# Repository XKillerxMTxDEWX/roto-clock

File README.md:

# roto-clock
Arduino powered spinning clock display.

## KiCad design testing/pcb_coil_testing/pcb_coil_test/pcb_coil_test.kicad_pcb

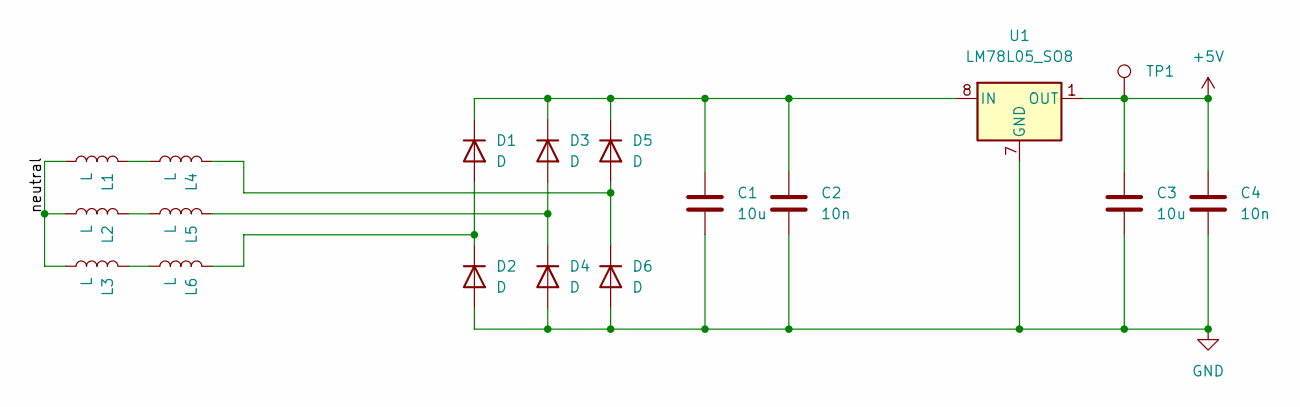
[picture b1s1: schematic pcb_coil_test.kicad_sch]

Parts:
C1, C3: 10u; CP_Radial_D5.0mm_P2.50mm
C2, C4: 10n; C_Rect_L7.0mm_W2.0mm_P5.00mm
D1, D2, D3, D4, D5, D6: D; D_A-405_P10.16mm_Horizontal
L1, L2, L3, L4, L5, L6: L; pcb_coil
TP1: TestPoint; TestPoint_Keystone_5010-5014_Multipurpose
U1: LM78L05_SO8; SOIC-8_3.9x4.9mm_P1.27mm

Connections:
+5V: C3.1, C4.1, TP1.1, U1.1 (OUT)
/neutral: L1.1, L2.1, L3.1
GND: C1.2, C2.2, C3.2, C4.2, D2.2 (A), D4.2 (A), D6.2 (A), U1.2 (GND), U1.3 (GND), U1.6 (GND), U1.7 (GND)
unnamed: C1.1, C2.1, D1.1 (K), D3.1 (K), D5.1 (K), U1.8 (IN)
unnamed: D1.2 (A), D2.1 (K), L6.2
unnamed: D3.2 (A), D4.1 (K), L5.2
unnamed: D5.2 (A), D6.1 (K), L4.2
unnamed: L1.2, L4.1
unnamed: L2.2, L5.1
unnamed: L3.2, L6.1

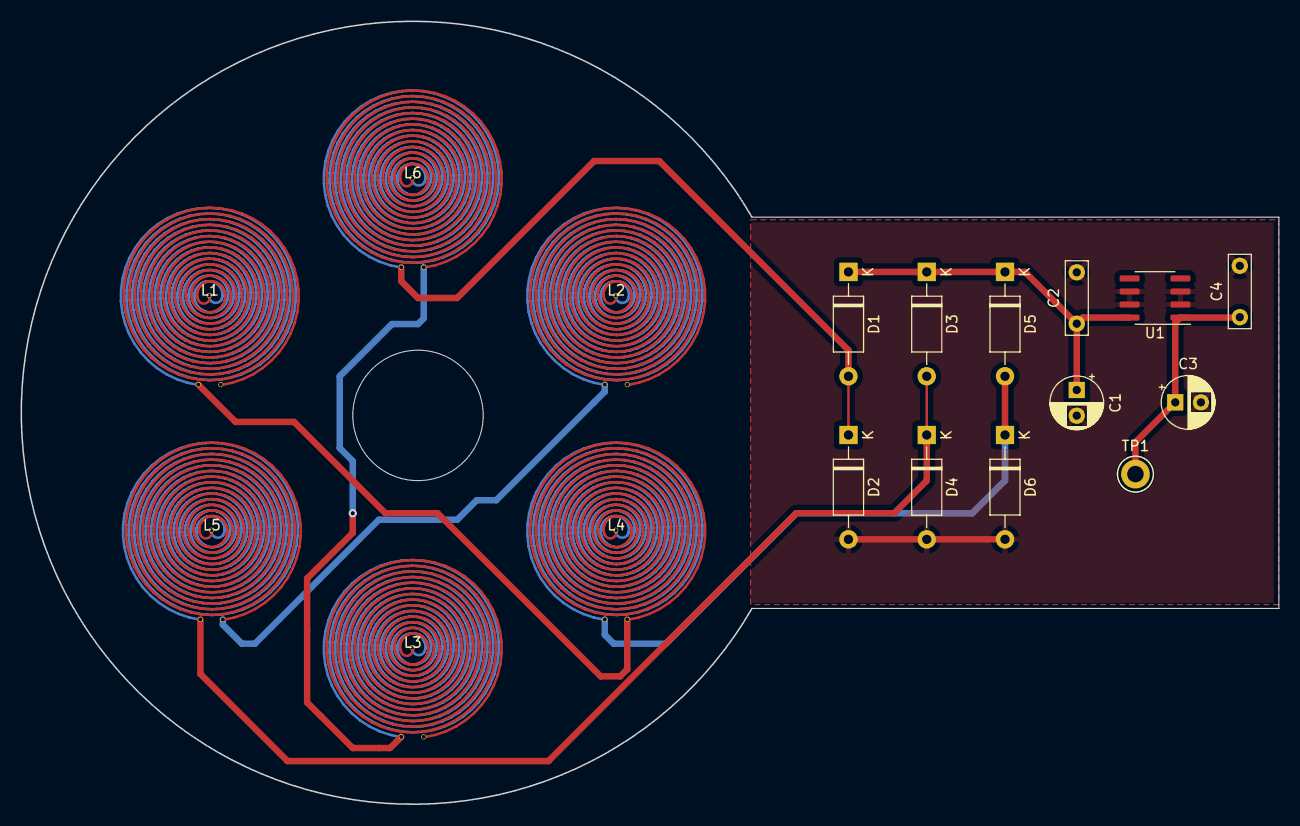
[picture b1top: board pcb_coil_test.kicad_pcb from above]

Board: 2 copper layers, 122.4 x 76.2 mm, 18 parts (0 on the bottom side), 10 nets.

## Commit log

2022-07-25 initial setup commit
2022-07-27 started work on coil footprint genrating script
2022-07-28 ordered pcb coil testing boards
